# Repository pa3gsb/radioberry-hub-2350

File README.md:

# RadioBerry SDR Meets the RP2350

*Introducing the RadioBerry Hub 2350 — an Ethernet hub for SDR and radio control*

RadioBerry began as a radio card for the Raspberry Pi, bringing together an
AD9866 mixed-signal front end, an FPGA, and open-source software to build an
SDR transceiver. It gives radio amateurs an opportunity to experiment with
the complete radio: hardware, gateware, signal processing, and the software
used to operate it. [More about RadioBerry](https://pa3gsb.github.io/projects/radioberry/).

As the project develops, new ideas continue to emerge. One question led to
the RadioBerry Hub 2350: how much of the work normally handled by the
Raspberry Pi could be performed by a small microcontroller?

The idea originated during development of the Raspberry Pi 5 RadioBerry
driver. Its use of Programmable Input/Output, or PIO, suggested another
possibility. The RP2350 also provides PIO state machines, which can handle
carefully timed communication with external hardware. Could this provide
a practical interface between a microcontroller and the RadioBerry FPGA?

Juan, WP3DN, pointed me towards the Waveshare RP2350 Pi Zero board.
Experiments with that board provided a starting point for exploring the
idea. From there, the next step was to design a dedicated board for
RadioBerry, with the connections needed for Ethernet operation and future
radio-control applications.

The result is the **RadioBerry Hub 2350**, or **RB Hub 2350** for short.

The board follows the familiar Raspberry Pi form factor and provides the
standard 40-pin connection for the RadioBerry card. The FPGA continues to
perform the radio's digital downconversion and upconversion, while the
RP2350 handles communication, control, and application firmware. At
startup, the microcontroller also loads the RadioBerry FPGA gateware.

Ethernet is an integral part of the design. A WIZnet W5500 controller
provides a 10/100 Mb Ethernet connection and handles TCP/IP functions in
hardware. It communicates with the RP2350 over SPI, giving the
microcontroller a practical way to exchange radio data and control
messages over the local network.

This continues an earlier direction explored with the
[RadioBerry JUICE board](https://www.pa3gsb.nl/2021/05/31/radioberry-juice/):
making RadioBerry accessible through different interfaces and computing
platforms. The Hub 2350 brings that exploration into a dedicated
microcontroller-based design.

Two firmware applications demonstrate what the new hardware can do.

The first implements **OpenHPSDR Protocol 1**. In this arrangement, the Hub
2350 acts as the Ethernet-connected host for the RadioBerry card.
Compatible SDR software on a computer receives the IQ samples and
provides demodulation, audio processing, and the operating interface.

This allows the existing RadioBerry card to become a network-connected
receiver, with the embedded firmware taking care of the radio-side startup
and communication. The current implementation supports receive operation.

The second application explores a different way of using the board:
**accessing RadioBerry directly from a web browser**.

A computer, laptop, or tablet on the same local network can open the
board's address and load its radio interface. The board serves the page
itself, including a spectrum display, waterfall, frequency controls, and
receiver gain adjustment. There is no separate web server to install or
maintain.

For a demonstration, this makes the setup particularly approachable.
Connect the radio to Ethernet, open a browser on a local device, and
interact with the board. It shows how a small amount of hardware can
provide both a radio interface and a network service.

The experimental WebSDR application also brings DSP onto the RP2350. Its
receiver software includes AM, USB, and LSB demodulation, filtering, and
adjustable automatic gain control. The controller processes the IQ
samples locally and sends demodulated audio to the browser for playback.
Transmitting audio requires considerably less network traffic than
continuously transferring the complete IQ stream.

These DSP functions are being developed as reusable software components.
That makes them useful beyond the browser application: the same receiver
processing can support future experiments with local audio hardware,
physical controls, or a display.

The expansion connections provide room to explore those possibilities.
An additional board with microphone input, audio output, buttons, and a
small display could form the basis of a compact standalone radio. Other
possibilities include filter switching, RX/TX control, and communication
with a power-amplifier controller for information such as temperature or
forward and reflected power.

Those are directions for further development. The immediate work centres
on the prototype hardware, reliable receive operation, and the two
firmware applications. The browser receiver remains an experimental
application, with testing and refinement continuing alongside development.

The RadioBerry Hub 2350 opens another route for building and experimenting
with RadioBerry. Existing SDR software can operate the radio through
OpenHPSDR Protocol 1, while the WebSDR application explores direct browser
access and local signal processing. Both approaches use the same hardware
platform and leave room for further ideas from builders and developers.

Have fun experimenting!

73,  
Johan — PA3GSB

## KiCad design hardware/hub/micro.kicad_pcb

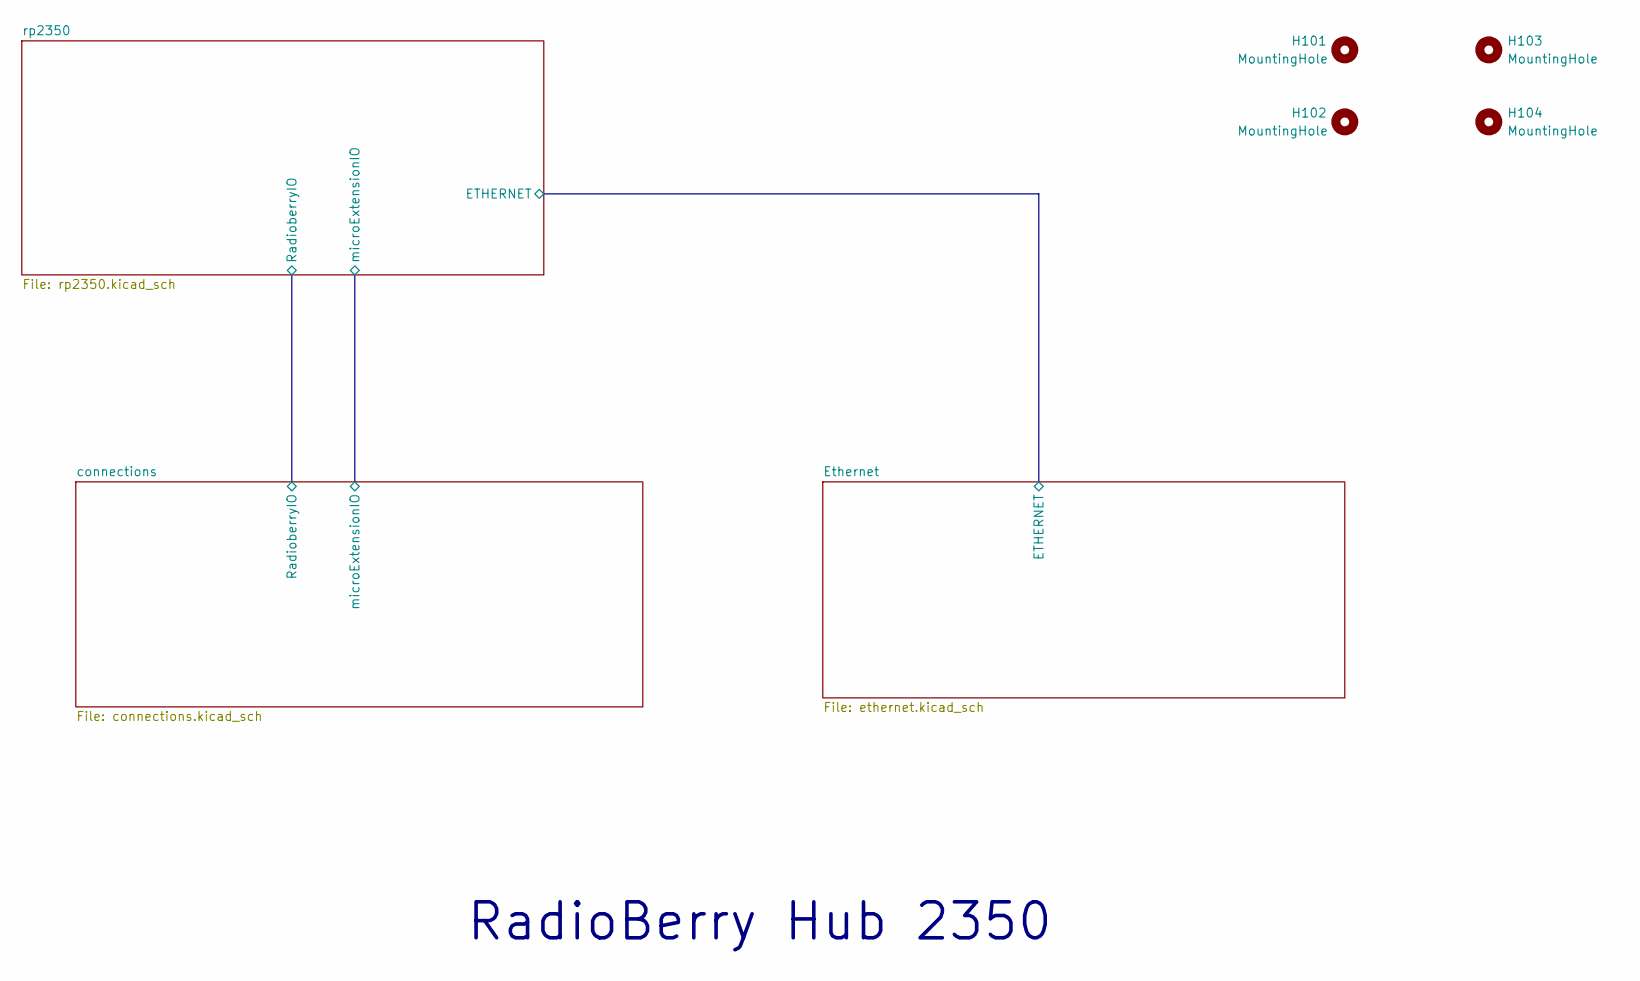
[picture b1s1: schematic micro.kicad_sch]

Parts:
H101, H102, H103, H104: MountingHole; MountingHole_2.7mm_M2.5_Pad

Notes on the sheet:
RadioBerry Hub 2350

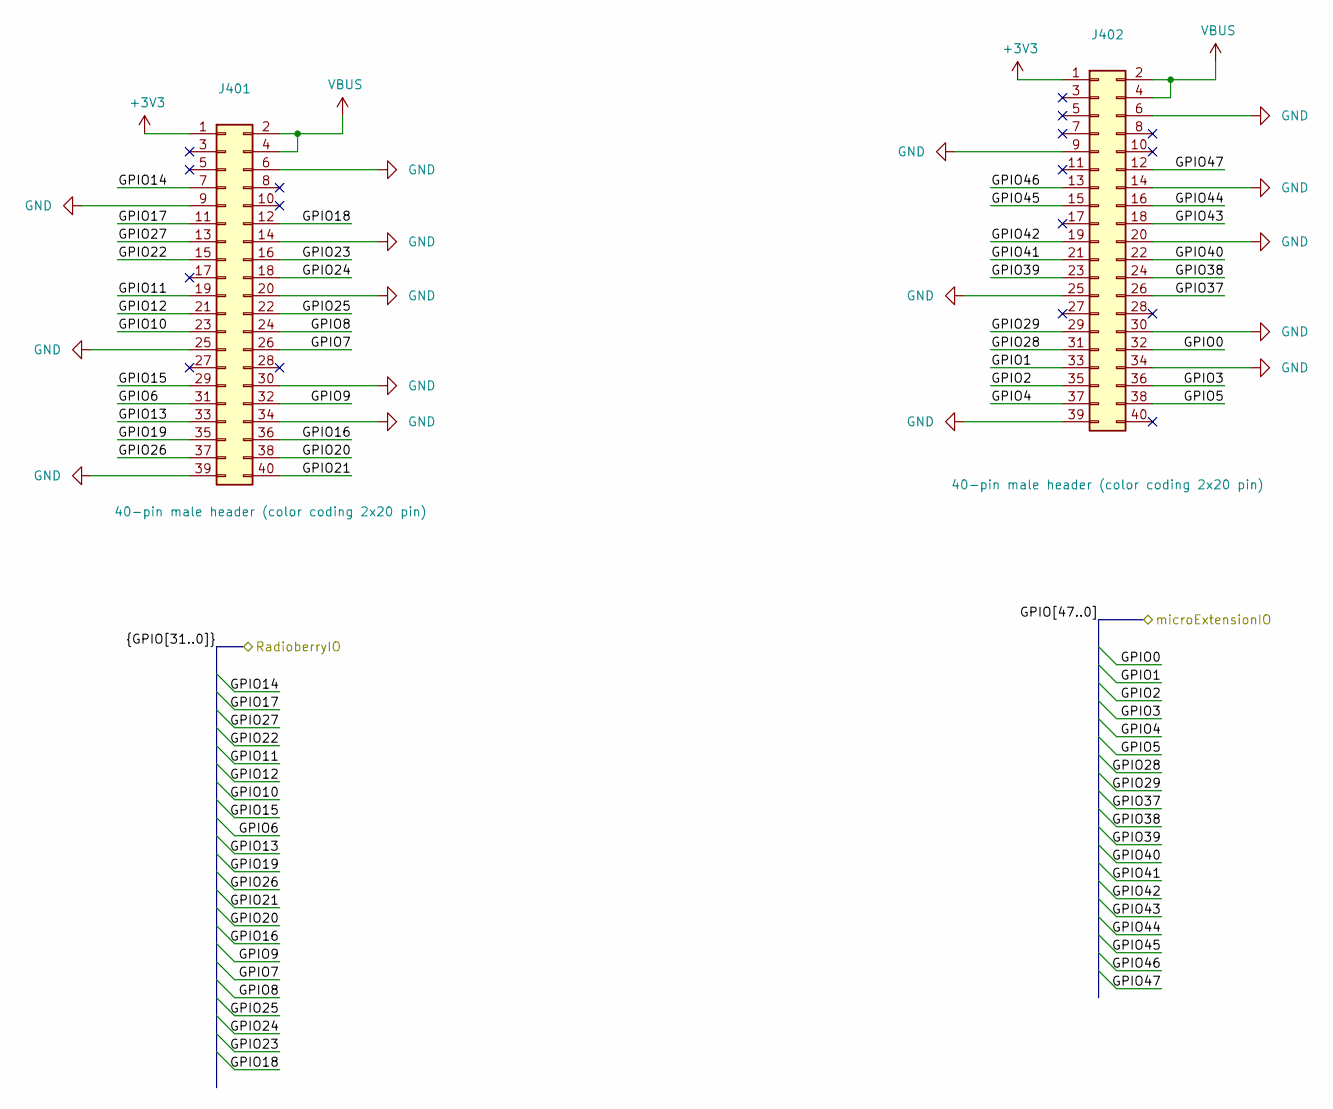
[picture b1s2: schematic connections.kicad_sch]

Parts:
J401: 40-pin male header (color coding 2x20 pin); PinHeader_2x20_P2.54mm_Vertical; MPN X6521WV-2x20H-C60D30; JLCPCB Part C725892
J402: 40-pin male header (color coding 2x20 pin); PinSocket_2x20_P2.54mm_Vertical; MPN X6521WV-2x20H-C60D30; JLCPCB Part C725892

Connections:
+3.3V: J401.1, J402.1; also elsewhere on the board
/connections/GPIO0: J402.32; also elsewhere on the board
/connections/GPIO1: J402.33; also elsewhere on the board
/connections/GPIO2: J402.35; also elsewhere on the board
/connections/GPIO3: J402.36; also elsewhere on the board
/connections/GPIO4: J402.37; also elsewhere on the board
/connections/GPIO5: J402.38; also elsewhere on the board
/connections/GPIO6: J401.31; also elsewhere on the board
/connections/GPIO7: J401.26; also elsewhere on the board
/connections/GPIO8: J401.24; also elsewhere on the board
/connections/GPIO9: J401.32; also elsewhere on the board
/connections/GPIO10: J401.23; also elsewhere on the board
/connections/GPIO11: J401.19; also elsewhere on the board
/connections/GPIO12: J401.21; also elsewhere on the board
/connections/GPIO13: J401.33; also elsewhere on the board
/connections/GPIO14: J401.7; also elsewhere on the board
/connections/GPIO15: J401.29; also elsewhere on the board
/connections/GPIO16: J401.36; also elsewhere on the board
/connections/GPIO17: J401.11; also elsewhere on the board
/connections/GPIO18: J401.12; also elsewhere on the board
/connections/GPIO19: J401.35; also elsewhere on the board
/connections/GPIO20: J401.38; also elsewhere on the board
/connections/GPIO21: J401.40; also elsewhere on the board
/connections/GPIO22: J401.15; also elsewhere on the board
/connections/GPIO23: J401.16; also elsewhere on the board
/connections/GPIO24: J401.18; also elsewhere on the board
/connections/GPIO25: J401.22; also elsewhere on the board
/connections/GPIO26: J401.37; also elsewhere on the board
/connections/GPIO27: J401.13; also elsewhere on the board
/connections/GPIO28: J402.31; also elsewhere on the board
/connections/GPIO29: J402.29; also elsewhere on the board
/connections/GPIO37: J402.26; also elsewhere on the board
/connections/GPIO38: J402.24; also elsewhere on the board
/connections/GPIO39: J402.23; also elsewhere on the board
/connections/GPIO40: J402.22; also elsewhere on the board
/connections/GPIO41: J402.21; also elsewhere on the board
/connections/GPIO42: J402.19; also elsewhere on the board
/connections/GPIO43: J402.18; also elsewhere on the board
/connections/GPIO44: J402.16; also elsewhere on the board
/connections/GPIO45: J402.15; also elsewhere on the board
/connections/GPIO46: J402.13; also elsewhere on the board
/connections/GPIO47: J402.12; also elsewhere on the board
GND: J401.6, J401.9, J401.14, J401.20, J401.25, J401.30, J401.34, J401.39, J402.6, J402.9, J402.14, J402.20, J402.25, J402.30, J402.34, J402.39; also elsewhere on the board
VBUS: J401.2, J401.4, J402.2, J402.4; also elsewhere on the board

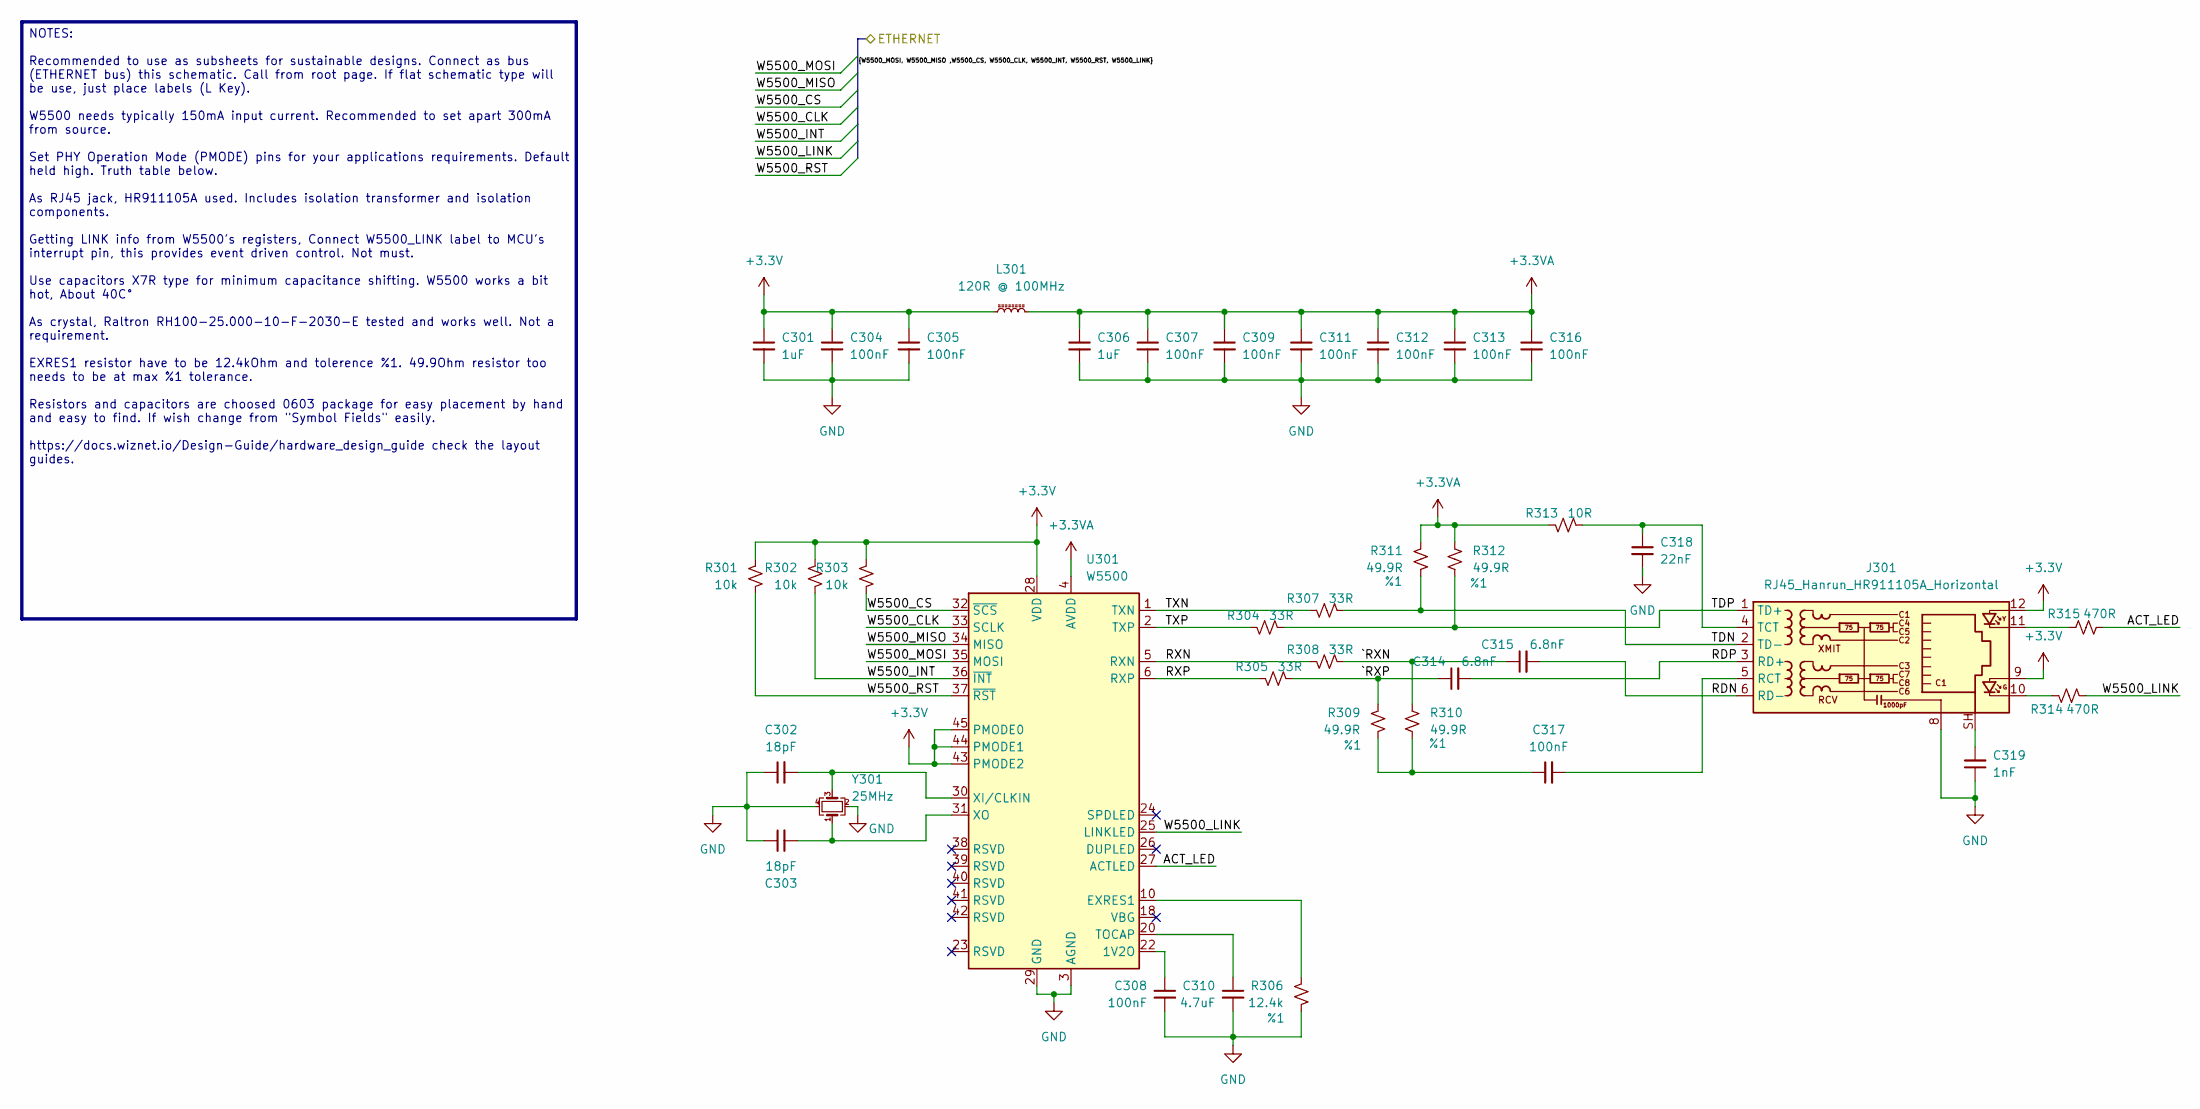
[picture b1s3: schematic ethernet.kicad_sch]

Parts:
C301, C306: 1uF; C_0603_1608Metric; PartNumber CL10A105KB8NNNC; JLCPCB Part C15849
C302, C303: 18pF; C_0603_1608Metric; PartNumber CC0603JRNPO9BN180; JLCPCB Part C1647
C304, C305, C307, C308, C309, C311, C312, C313, C316, C317: 100nF; C_0603_1608Metric; PartNumber CL10B104KB8NNNC; JLCPCB Part C14663
C310: 4.7uF; C_0603_1608Metric; PartNumber CL10B475KQ8NQNC; JLCPCB Part C19666
C314, C315: 6.8nF; C_0603_1608Metric; PartNumber CL10B682KB8NNNC; JLCPCB Part C1631
C318: 22nF; C_0603_1608Metric; PartNumber CL10B223KB8NNNC; JLCPCB Part C21122
C319: 1nF; C_1210_3225Metric; PartNumber CL32B102KJFNNNE; JLCPCB Part C527380
J301: RJ45_Hanrun_HR911105A_Horizontal; PartNumber HR911105A; JLCPCB Part C12074
L301: 120R @ 100MHz; L_0603_1608Metric; PartNumber BLM18KG121TN1D; JLCPCB Part C2943445
R301, R302, R303: 10k; R_0603_1608Metric; PartNumber AC0603JR-0710KL; JLCPCB Part C25804
R304, R305, R307, R308: 33R; R_0603_1608Metric; PartNumber RC0603JR-0733RL; JLCPCB Part C23140
R306: 12.4k; R_0603_1608Metric; Tolerance %1; PartNumber RC0603FR-0712K4L; JLCPCB Part C2930060
R309, R310, R311, R312: 49.9R; R_0603_1608Metric; Tolerance %1; PartNumber ERA-3AEB49R9V; JLCPCB Part C23185
R313: 10R; R_0603_1608Metric; PartNumber RC0603FR-0710RL; JLCPCB Part C22859
R314, R315: 470R; R_0603_1608Metric; PartNumber RC0603JR-07470RL; JLCPCB Part C23179
U301: W5500; LQFP-48_7x7mm_P0.5mm; PartNumber W5500; JLCPCB Part C32843
Y301: 25MHz; Crystal_SMD_Abracon_ABM8AIG-4Pin_3.2x2.5mm; PartNumber ABM8-25.000MHZ-D2Y-T; JLCPCB Part C179643

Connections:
+3.3V: C301.1, C304.1, C305.1, J301.9, J301.12, L301.1, R301.1, R302.1, R303.1, U301.28 (VDD), U301.43 (PMODE2), U301.44 (PMODE1), U301.45 (PMODE0); also elsewhere on the board
+3.3VA: C306.1, C307.1, C309.1, C311.1, C312.1, C313.1, C316.1, L301.2, R311.1, R312.1, R313.1, U301.4 (AVDD), U301.8 (AVDD), U301.11 (AVDD), U301.15 (AVDD), U301.17 (AVDD), U301.21 (AVDD)
/Ethernet/ACT_LED: R315.2, U301.27 (ACTLED)
/Ethernet/RDN: C315.2, J301.6 (RD-)
/Ethernet/RDP: C314.2, J301.3 (RD+)
/Ethernet/RXN: R308.1, U301.5 (RXN)
/Ethernet/RXP: R305.1, U301.6 (RXP)
/Ethernet/TDN: J301.2 (TD-), R307.2, R311.2
/Ethernet/TDP: J301.1 (TD+), R304.2, R312.2
/Ethernet/TXN: R307.1, U301.1 (TXN)
/Ethernet/TXP: R304.1, U301.2 (TXP)
/Ethernet/W5500_CLK: U301.33 (SCLK); also elsewhere on the board
/Ethernet/W5500_CS: R303.2, U301.32 (~SCS); also elsewhere on the board
/Ethernet/W5500_INT: R302.2, U301.36 (~INT); also elsewhere on the board
/Ethernet/W5500_LINK: R314.2, U301.25 (LINKLED); also elsewhere on the board
/Ethernet/W5500_MISO: U301.34 (MISO); also elsewhere on the board
/Ethernet/W5500_MOSI: U301.35 (MOSI); also elsewhere on the board
/Ethernet/W5500_RST: R301.2, U301.37 (~RST); also elsewhere on the board
/Ethernet/`RXN: C315.1, R308.2, R310.1
/Ethernet/`RXP: C314.1, R305.2, R309.1
GND: C301.2, C302.1, C303.1, C304.2, C305.2, C306.2, C307.2, C308.2, C309.2, C310.2, C311.2, C312.2, C313.2, C316.2, C318.2, C319.1, J301.8, R306.2, U301.3 (AGND), U301.9 (AGND), U301.14 (AGND), U301.16 (AGND), U301.19 (AGND), U301.29 (GND), U301.48 (AGND), Y301.2, Y301.4; also elsewhere on the board
unnamed: C317.1, R309.2, R310.2
unnamed: C319.2, J301.SH
unnamed: J301.10, R314.1
unnamed: J301.11, R315.1
unnamed: C317.2, J301.5 (RCT)
unnamed: C318.1, J301.4 (TCT), R313.2
unnamed: C308.1, U301.22 (1V2O)
unnamed: R306.1, U301.10 (EXRES1)
unnamed: C310.1, U301.20 (TOCAP)
unnamed: C302.2, U301.30 (XI/CLKIN), Y301.3
unnamed: C303.2, U301.31 (XO), Y301.1

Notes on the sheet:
NOTES: Recommended to use as subsheets for sustainable designs. Connect as bus (ETHERNET bus) this schematic. Call from root page. If flat schematic type will be use, just place labels (L Key). W5500 needs typically 150mA input current. Recommended to set apart 300mA from source. Set PHY Operation 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

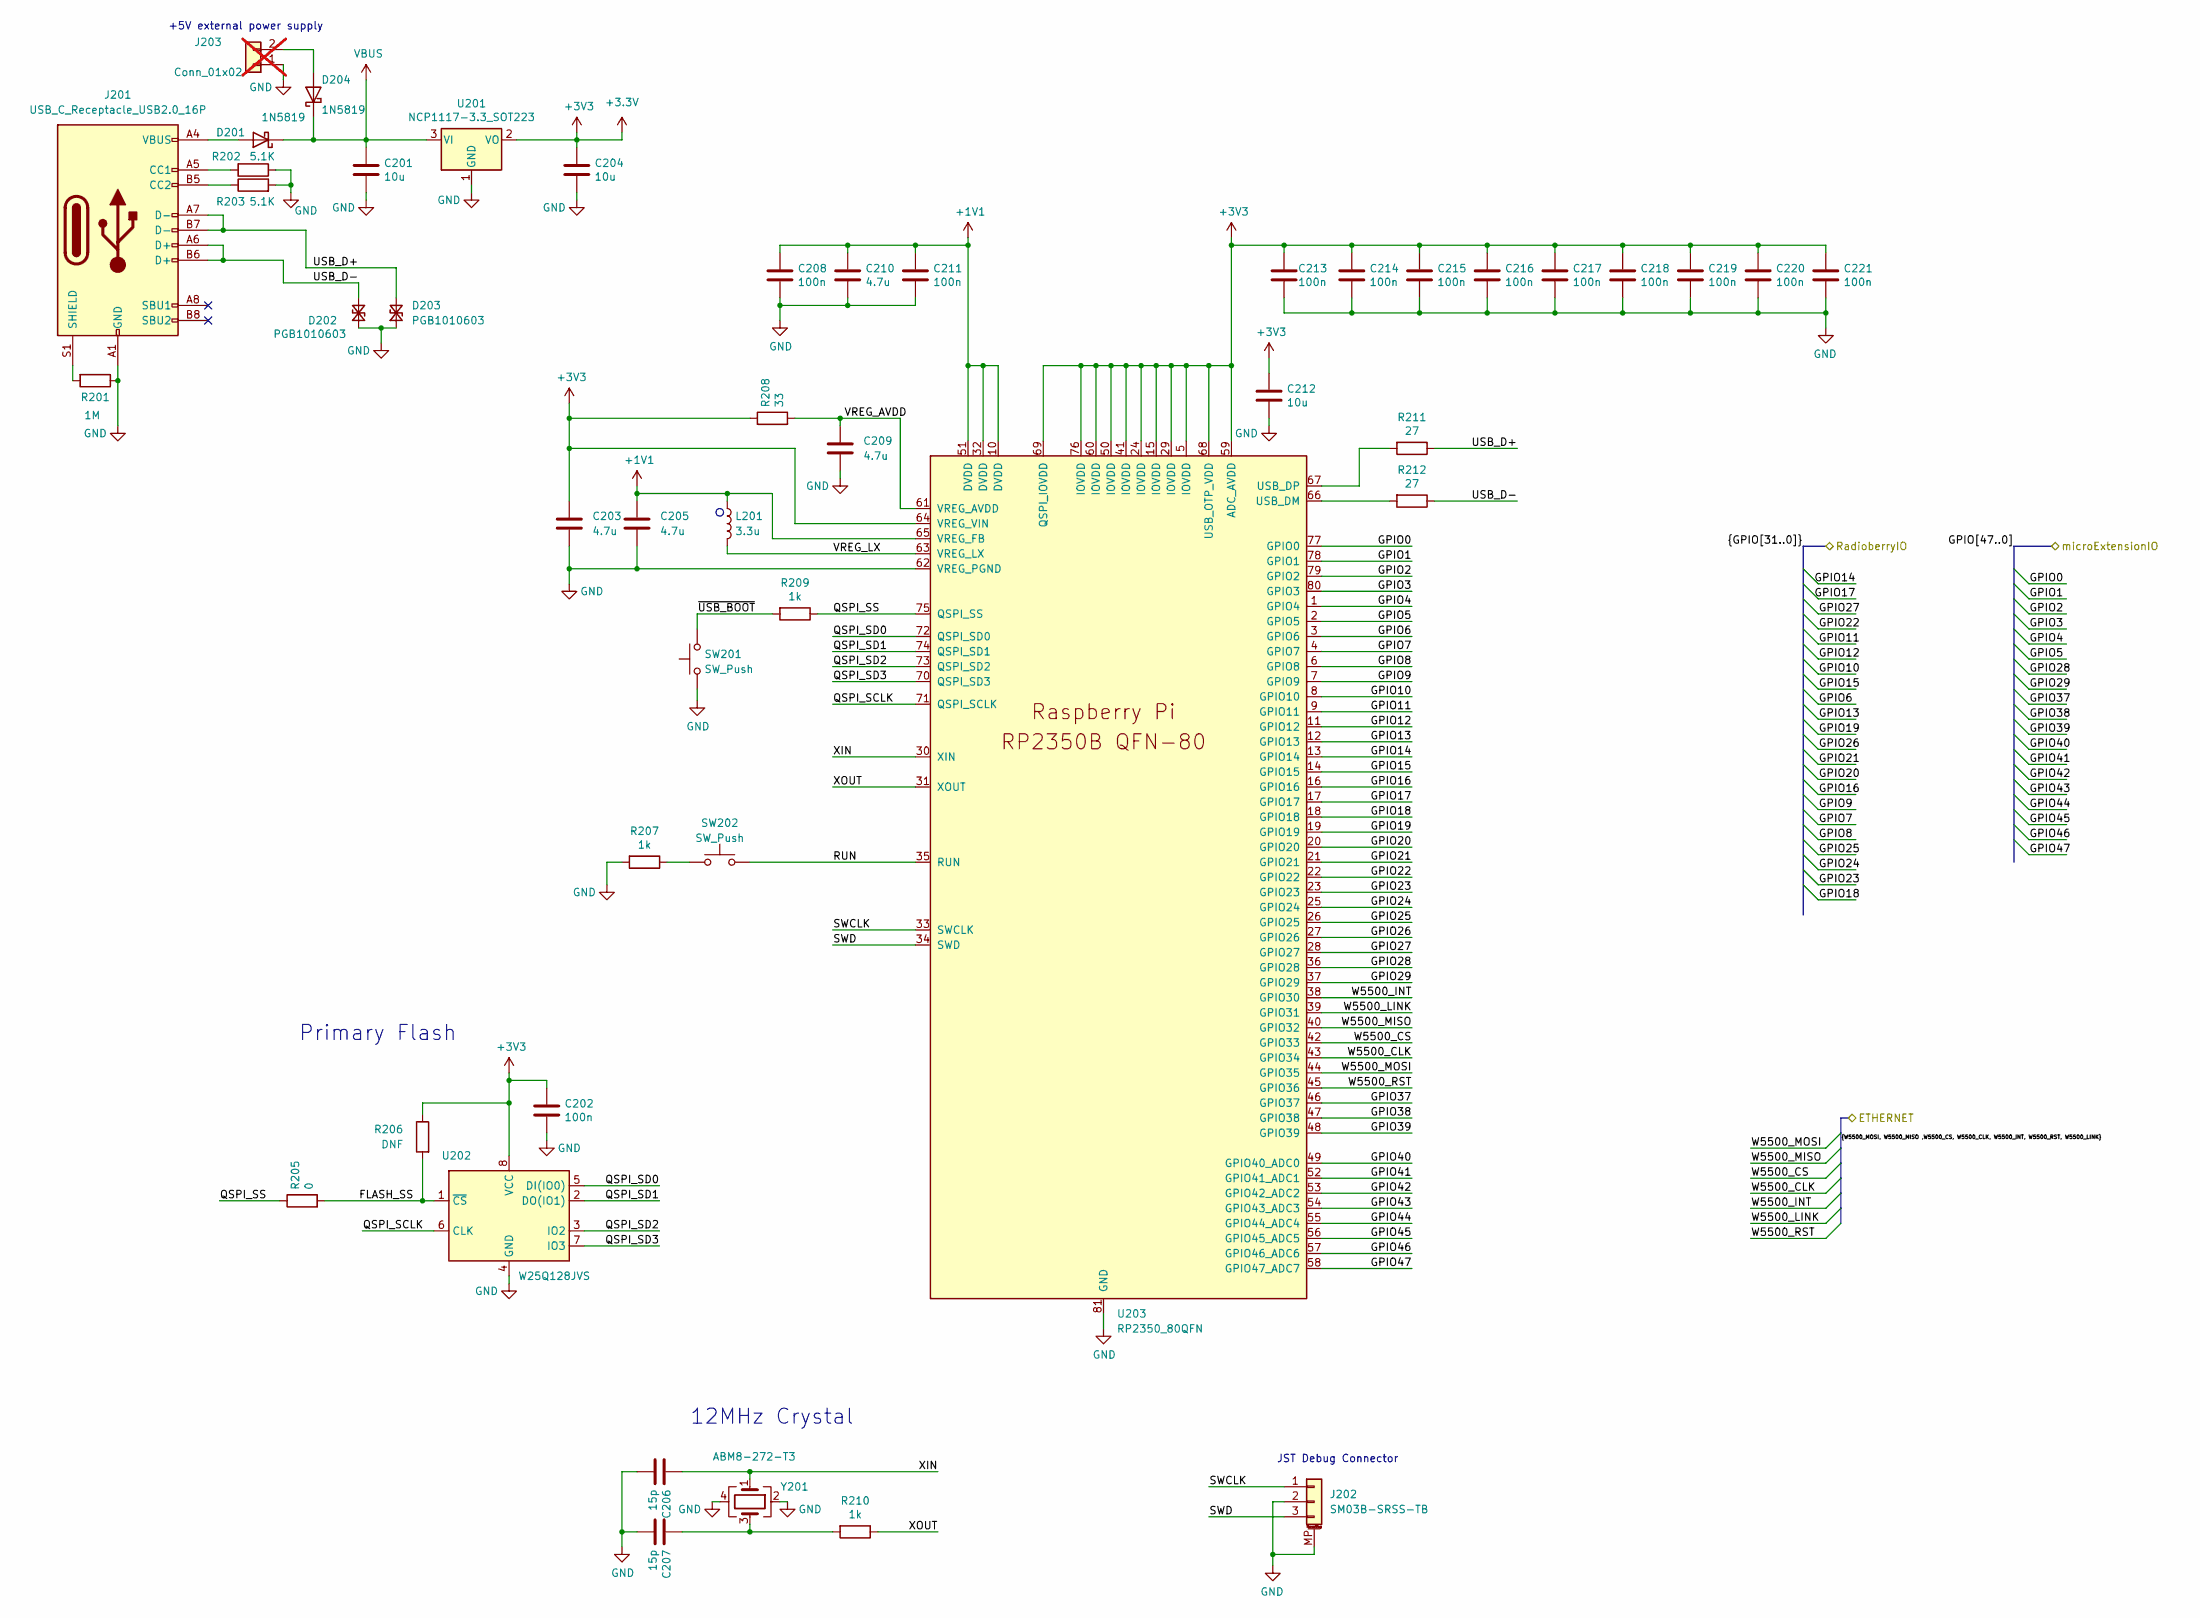
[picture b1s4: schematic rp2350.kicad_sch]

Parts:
C201, C204, C212: 10u; C_0805_2012Metric; MPN GRM21BR61H106KE43L; JLCPCB Part C440198
C202, C208, C211, C213, C214, C215, C216, C217, C218, C219, C220, C221: 100n; C_0402_1005Metric; MPN CL05B104KO5NNNC; JLCPCB Part C1525
C203, C205, C209, C210: 4.7u; C_0402_1005Metric; MPN GRM155R61A475KEAAD; JLCPCB Part C77004
C206, C207: 15p; C_0402_1005Metric; MPN 0402CG150J500NT; JLCPCB Part C1548
D201, D204: 1N5819; D_SOD-323; MPN 1N5819WS; JLCPCB Part C191023
D202, D203: PGB1010603; D_0603_1608Metric_Pad1.05x0.95mm_HandSolder; MPN PGB1010603NR; JLCPCB Part C10677
J201: USB_C_Receptacle_USB2.0_16P; TYPE-C-31-M-12; MPN TYPE-C-31-M-12; JLCPCB Part C165948
J202: SM03B-SRSS-TB; JST_SH_SM03B-SRSS-TB_1x03-1MP_P1.00mm_Horizontal; MPN SM03B-SRSS-TB(LF)(SN); JLCPCB Part C160403
J203: Conn_01x02; PinHeader_1x02_P2.54mm_Vertical; not fitted
L201: 3.3u; L_pol_2016; MPN AOTA-B201610S3R3-101-T; JLCPCB Part C42411119
R201: 1M; R_0603_1608Metric; MPN 0603WAF1004T5E; JLCPCB Part C22935
R202, R203: 5.1K; R_0603_1608Metric; MPN 0603WAF5101T5E; JLCPCB Part C23186
R205: 0; R_0603_1608Metric; MPN 0603WAF0000T5E; JLCPCB Part C21189
R206: DNF; R_0603_1608Metric
R207, R209: 1k; R_0603_1608Metric; MPN 0603WAF1001T5E; JLCPCB Part C21190
R208: 33; R_0402_1005Metric; MPN 0402WGF330JTCE; JLCPCB Part C25105
R210: 1k; R_0402_1005Metric; MPN 0402WGD1001TCE; JLCPCB Part C407754
R211, R212: 27; R_0402_1005Metric; MPN 0402WGJ0270TCE; JLCPCB Part C25156
SW201, SW202: SW_Push; SW_Push_1P1T_NO_Vertical_Wuerth_434133025816; MPN 434133025816; JLCPCB Part C5504987
U201: NCP1117-3.3_SOT223; SOT-223-3_TabPin2; MPN NCP1117ST33T3G; JLCPCB Part C26537
U202: W25Q128JVS; SOIC-8_5.3x5.3mm_P1.27mm; MPN W25Q128JVSIQ; JLCPCB Part C97521
U203: RP2350_80QFN; RP2350-QFN-80-1EP_10x10_P0.4mm_EP3.4x3.4mm_ThermalVias; PartNumber RP2350B; JLCPCB Part C42415655
Y201: ABM8-272-T3; Crystal_SMD_3225-4Pin_3.2x2.5mm; MPN ABM8-272-T3; JLCPCB Part C20625731

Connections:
+1V1: C205.1, C208.1, C210.1, C211.1, L201.1, U203.10 (DVDD), U203.32 (DVDD), U203.51 (DVDD), U203.65 (VREG_FB)
+3.3V: C202.1, C203.1, C204.1, C212.1, C213.1, C214.1, C215.1, C216.1, C217.1, C218.1, C219.1, C220.1, C221.1, R206.1, R208.1, U201.2 (VO), U202.8 (VCC), U203.5 (IOVDD), U203.15 (IOVDD), U203.24 (IOVDD), U203.29 (IOVDD), U203.41 (IOVDD), U203.50 (IOVDD), U203.59 (ADC_AVDD), U203.60 (IOVDD), U203.64 (VREG_VIN), U203.68 (USB_OTP_VDD), U203.69 (QSPI_IOVDD), U203.76 (IOVDD); also elsewhere on the board
/Ethernet/W5500_CLK: U203.43 (GPIO34); also elsewhere on the board
/Ethernet/W5500_CS: U203.42 (GPIO33); also elsewhere on the board
/Ethernet/W5500_INT: U203.38 (GPIO30); also elsewhere on the board
/Ethernet/W5500_LINK: U203.39 (GPIO31); also elsewhere on the board
/Ethernet/W5500_MISO: U203.40 (GPIO32); also elsewhere on the board
/Ethernet/W5500_MOSI: U203.44 (GPIO35); also elsewhere on the board
/Ethernet/W5500_RST: U203.45 (GPIO36); also elsewhere on the board
/connections/GPIO0: U203.77 (GPIO0); also elsewhere on the board
/connections/GPIO1: U203.78 (GPIO1); also elsewhere on the board
/connections/GPIO2: U203.79 (GPIO2); also elsewhere on the board
/connections/GPIO3: U203.80 (GPIO3); also elsewhere on the board
/connections/GPIO4: U203.1 (GPIO4); also elsewhere on the board
/connections/GPIO5: U203.2 (GPIO5); also elsewhere on the board
/connections/GPIO6: U203.3 (GPIO6); also elsewhere on the board
/connections/GPIO7: U203.4 (GPIO7); also elsewhere on the board
/connections/GPIO8: U203.6 (GPIO8); also elsewhere on the board
/connections/GPIO9: U203.7 (GPIO9); also elsewhere on the board
/connections/GPIO10: U203.8 (GPIO10); also elsewhere on the board
/connections/GPIO11: U203.9 (GPIO11); also elsewhere on the board
/connections/GPIO12: U203.11 (GPIO12); also elsewhere on the board
/connections/GPIO13: U203.12 (GPIO13); also elsewhere on the board
/connections/GPIO14: U203.13 (GPIO14); also elsewhere on the board
/connections/GPIO15: U203.14 (GPIO15); also elsewhere on the board
/connections/GPIO16: U203.16 (GPIO16); also elsewhere on the board
/connections/GPIO17: U203.17 (GPIO17); also elsewhere on the board
/connections/GPIO18: U203.18 (GPIO18); also elsewhere on the board
/connections/GPIO19: U203.19 (GPIO19); also elsewhere on the board
/connections/GPIO20: U203.20 (GPIO20); also elsewhere on the board
/connections/GPIO21: U203.21 (GPIO21); also elsewhere on the board
/connections/GPIO22: U203.22 (GPIO22); also elsewhere on the board
/connections/GPIO23: U203.23 (GPIO23); also elsewhere on the board
/connections/GPIO24: U203.25 (GPIO24); also elsewhere on the board
/connections/GPIO25: U203.26 (GPIO25); also elsewhere on the board
/connections/GPIO26: U203.27 (GPIO26); also elsewhere on the board
/connections/GPIO27: U203.28 (GPIO27); also elsewhere on the board
/connections/GPIO28: U203.36 (GPIO28); also elsewhere on the board
/connections/GPIO29: U203.37 (GPIO29); also elsewhere on the board
/connections/GPIO37: U203.46 (GPIO37); also elsewhere on the board
/connections/GPIO38: U203.47 (GPIO38); also elsewhere on the board
/connections/GPIO39: U203.48 (GPIO39); also elsewhere on the board
/connections/GPIO40: U203.49 (GPIO40_ADC0); also elsewhere on the board
/connections/GPIO41: U203.52 (GPIO41_ADC1); also elsewhere on the board
/connections/GPIO42: U203.53 (GPIO42_ADC2); also elsewhere on the board
/connections/GPIO43: U203.54 (GPIO43_ADC3); also elsewhere on the board
/connections/GPIO44: U203.55 (GPIO44_ADC4); also elsewhere on the board
/connections/GPIO45: U203.56 (GPIO45_ADC5); also elsewhere on the board
/connections/GPIO46: U203.57 (GPIO46_ADC6); also elsewhere on the board
/connections/GPIO47: U203.58 (GPIO47_ADC7); also elsewhere on the board
/rp2350/FLASH_SS: R205.2, R206.2, U202.1 (~CS)
/rp2350/QSPI_SCLK: U202.6 (CLK), U203.71 (QSPI_SCLK)
/rp2350/QSPI_SD0: U202.5 (DI(IO0)), U203.72 (QSPI_SD0)
/rp2350/QSPI_SD1: U202.2 (DO(IO1)), U203.74 (QSPI_SD1)
/rp2350/QSPI_SD2: U202.3 (IO2), U203.73 (QSPI_SD2)
/rp2350/QSPI_SD3: U202.7 (IO3), U203.70 (QSPI_SD3)
/rp2350/QSPI_SS: R205.1, R209.1, U203.75 (QSPI_SS)
/rp2350/RUN: SW202.2, U203.35 (RUN)
/rp2350/SWCLK: J202.1, U203.33 (SWCLK)
/rp2350/SWD: J202.3, U203.34 (SWD)
/rp2350/USB_D+: D203.2 (A2), J201.A7 (D-), J201.B7 (D-), R211.1
/rp2350/USB_D-: D202.2 (A2), J201.A6 (D+), J201.B6 (D+), R212.1
/rp2350/VREG_AVDD: C209.1, R208.2, U203.61 (VREG_AVDD)
/rp2350/VREG_LX: L201.2, U203.63 (VREG_LX)
/rp2350/XIN: C206.1, U203.30 (XIN), Y201.1
/rp2350/XOUT: R210.1, U203.31 (XOUT)
/rp2350/~USB_BOOT: R209.2, SW201.2
GND: C201.2, C202.2, C203.2, C204.2, C205.2, C206.2, C207.2, C208.2, C209.2, C210.2, C211.2, C212.2, C213.2, C214.2, C215.2, C216.2, C217.2, C218.2, C219.2, C220.2, C221.2, D202.1 (A1), D203.1 (A1), J201.A1 (GND), J201.A12 (GND), J201.B1 (GND), J201.B12 (GND), J202.2, J202.MP (MountPin), J203.1, R201.1, R202.1, R203.2, R207.2, SW201.1, U201.1 (GND), U202.4 (GND), U203.62 (VREG_PGND), U203.81 (GND), Y201.2, Y201.4; also elsewhere on the board
unnamed: C207.1, R210.2, Y201.3
unnamed: D201.2 (A), J201.A4 (VBUS), J201.A9 (VBUS), J201.B4 (VBUS), J201.B9 (VBUS)
unnamed: D204.2 (A), J203.2
unnamed: J201.A5 (CC1), R202.2
unnamed: J201.B5 (CC2), R203.1
unnamed: J201.S1 (SHIELD), R201.2
unnamed: R207.1, SW202.1
unnamed: R212.2, U203.66 (USB_DM)
unnamed: R211.2, U203.67 (USB_DP)
VBUS: C201.1, D201.1 (K), D204.1 (K), U201.3 (VI); also elsewhere on the board

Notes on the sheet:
+5V external power supply
JST Debug Connector
12MHz Crystal
Primary Flash

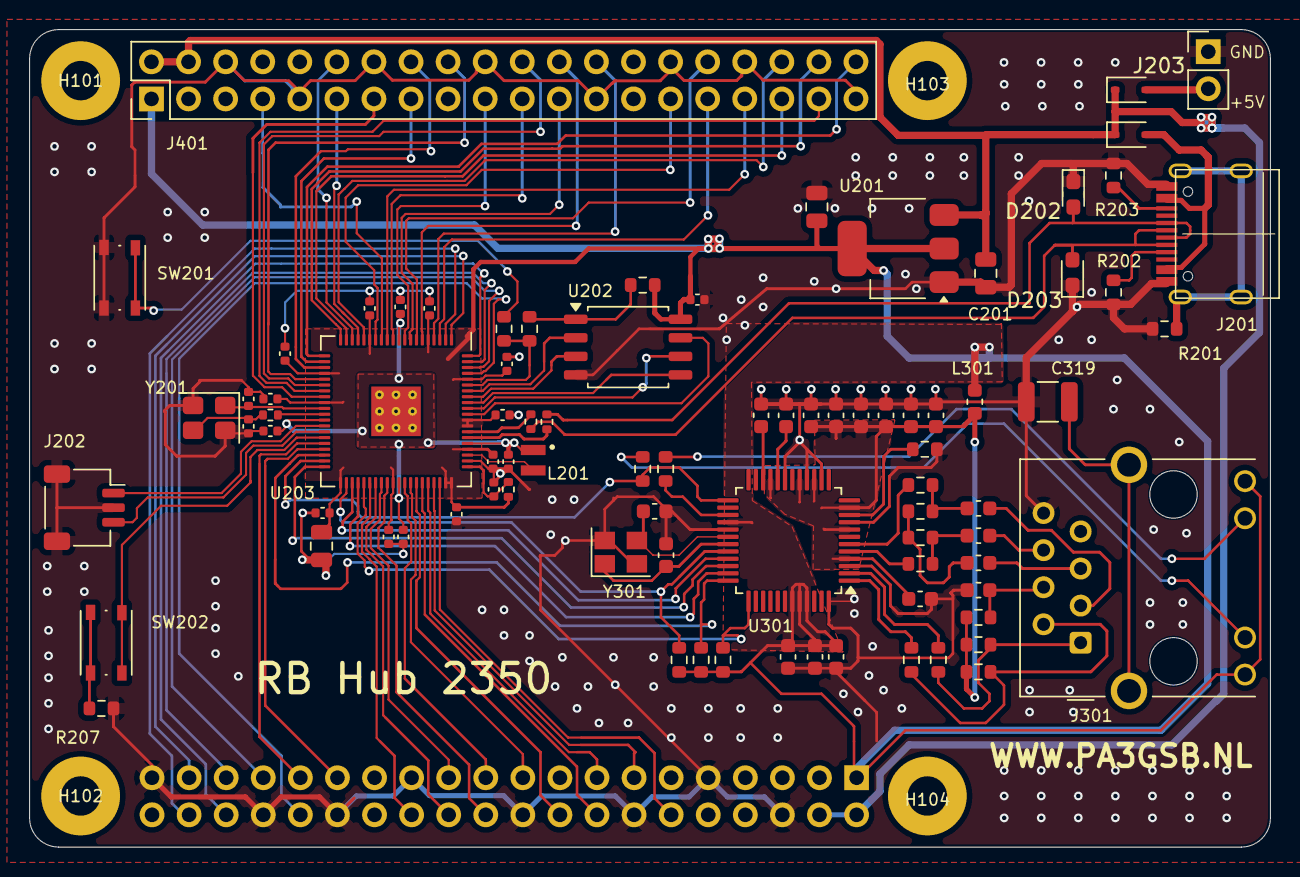
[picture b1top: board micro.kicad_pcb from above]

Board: 2 copper layers, 85.0 x 56.0 mm, 90 parts (1 on the bottom side), 101 nets.

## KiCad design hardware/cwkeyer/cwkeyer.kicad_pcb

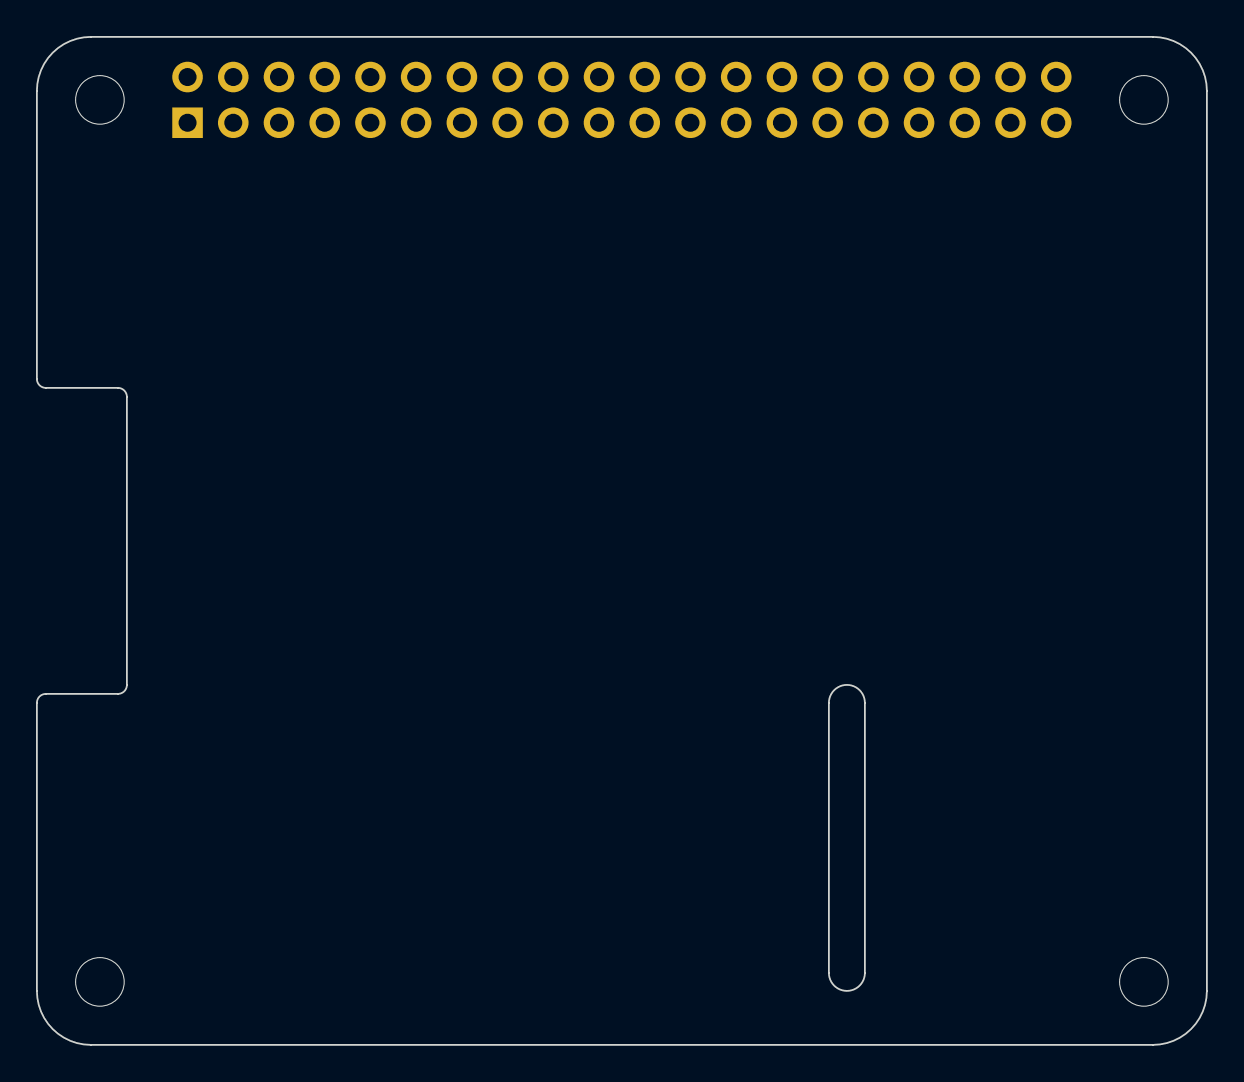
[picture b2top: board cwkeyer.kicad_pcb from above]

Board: 2 copper layers, 65.0 x 56.0 mm, 5 parts (1 on the bottom side), 3 nets, no tracks yet.

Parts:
J1: GPIO; PinSocket_2x20_P2.54mm_Vertical
MH1, MH2, MH3, MH4: MountingHole_2.7mm_M2.5

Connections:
+3V3: J1.1, J1.17
+5V: J1.2, J1.4
GND: J1.6, J1.9, J1.14, J1.20, J1.25, J1.30, J1.34, J1.39

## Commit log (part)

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2026-05-28 hardware kicad added
